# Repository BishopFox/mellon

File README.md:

## OSDP Vulnerabilities this Exploits
OSDP attack tool (and the Elvish word for friend)

### Attack #1: Encryption is Optional

OSDP supports, but doesn't strictly *require*, encryption. So your connection might not even be encrypted at all. Attack #1 is just to passively listen and see if you can read the card numbers on the wire.

### Attack #2: Downgrade Attack

Just because the controller and reader *support* encryption doesn't mean they're configured to *require* it be used. An attacker can modify the reader's capability reply message (osdp_PDCAP) to advertise that it doesn't support encryption. When this happens, some controllers will barrel ahead without encryption.

### Attack #3: Install-mode Attack

OSDP has a quasi-official “install mode” that applies to both readers and controllers. As the name suggests, it’s supposed to be used when first setting up a reader. What it does is essentially allow readers to ask the controller for what the base encryption key (the SCBK) is. If the controller is configured to be persistently in install-mode, then an attacker can show up on the wire and request the SCBK. 

### Attack #4: Weak Keys

OSDP sample code often comes with hardcoded encryption keys. Clearly these are meant to be samples, where the user is supposed to generate keys in a secure way on their own. But this is not explained or made simple for the user, however. And anyone who’s been in security long enough knows that whatever’s the default is likely to be there in production. 

So as an attack vector, when the link between reader and controller is encrypted, it’s worth a shot to enumerate some common weak keys. Now these are 128-bit AES keys, so we’re not going to be able to enumerate them all. Or even a meaningful portion of them. But what we can do is hit some common patterns that you see when someone hardcodes a key: 

- All single-byte values. [0x04, 0x04, 0x04, 0x04 …]
- All monotonically increasing byte values. [0x01, 0x02, 0x03, 0x04, …]
- All monotonically decreasing byte values. [0x0A, 0x09, 0x08, 0x07, …]

### Attack #5: Keyset Capture

OSDP has no in-band mechansim for key exchange. What this means is that an attacker can:

- Insert a covert listening device onto the wire. 
- Break / factory reset / disable the reader.
- Wait for someone from IT to come and replace the reader.
- Capture the keyset message (osdp_KEYSET) when the reader is first setup.
- Decrypt all future messages.

## Getting A Testbed Setup (Linux/MacOS)

You'll find proof-of-concept code for each of these attacks in `attack_osdp.py`. Checkout the `--help` command for more details on usage. This is a Python script, meant to be run from a laptop with USB<-->RS485 adapters [like one of these](https://www.amazon.com/Serial-Converter-Adapter-Supports-Windows/dp/B0195ZD3P4/). So you'll probably want to pick some of those up. Doesn't have to be that model, though.

If you have a controller you want to test, then great. Use that. If you don't, then we have an intentionally-vulnerable OSDP controller that you can use here: `vulnserver.py`. 

Some of the attacks in `attack_osdp.py` will expect to be as a full MitM between a functioning reader and controller. To test these, you might need *three* USB<-->RS485 adapters, hooked together with a breadboard.

### Additional Medium / Low Risk Issues

These issues are not, in isolation, exploitable but nonetheless represent a weakening of the protocol, implementation, or overall system.

- MACs are truncated to 32 bits "to reduce overhead". This is _very_ nearly (but not quite in our calculation) within practical exploitable range.
- IVs (which are derived from MACs) are similarly reduced to 32 bits of entropy. This will cause IV reuse, which is a big red flag for a protocol.
- Session keys are only generated using 48 bits of entropy from the controller RNG nonce. This appears to not be possible for an observing attacker to enumerate offline, however. (Unless we're missing something, in which case this would become a _critical_ issue.)
- Sequence numbers consist of only 2 bits, not providing sufficient liveness.
- CBC-mode encryption is used. GCM would be a more modern block cipher mode appropriate for network protocols.
- SCS modes 15 & 16 are essentially "null ciphers", and should not exist. They don't encrypt data.
- The OSDP command byte is always unencrypted, even in the middle of a Secure Channel session. This is a huge benefit to attackers, making attack tools much easier to write. It means that an attacker can always see what "type" of packet is being sent, even if it's otherwise encrypted. Attackers can tell when people badge in, when the LED lights up, etc... This is not information that should be in plaintext.
- SCBK-D (a hardcoded "default" encryption key) provides no security and should be removed. It serves only to obfuscate and provide a false sense of security.

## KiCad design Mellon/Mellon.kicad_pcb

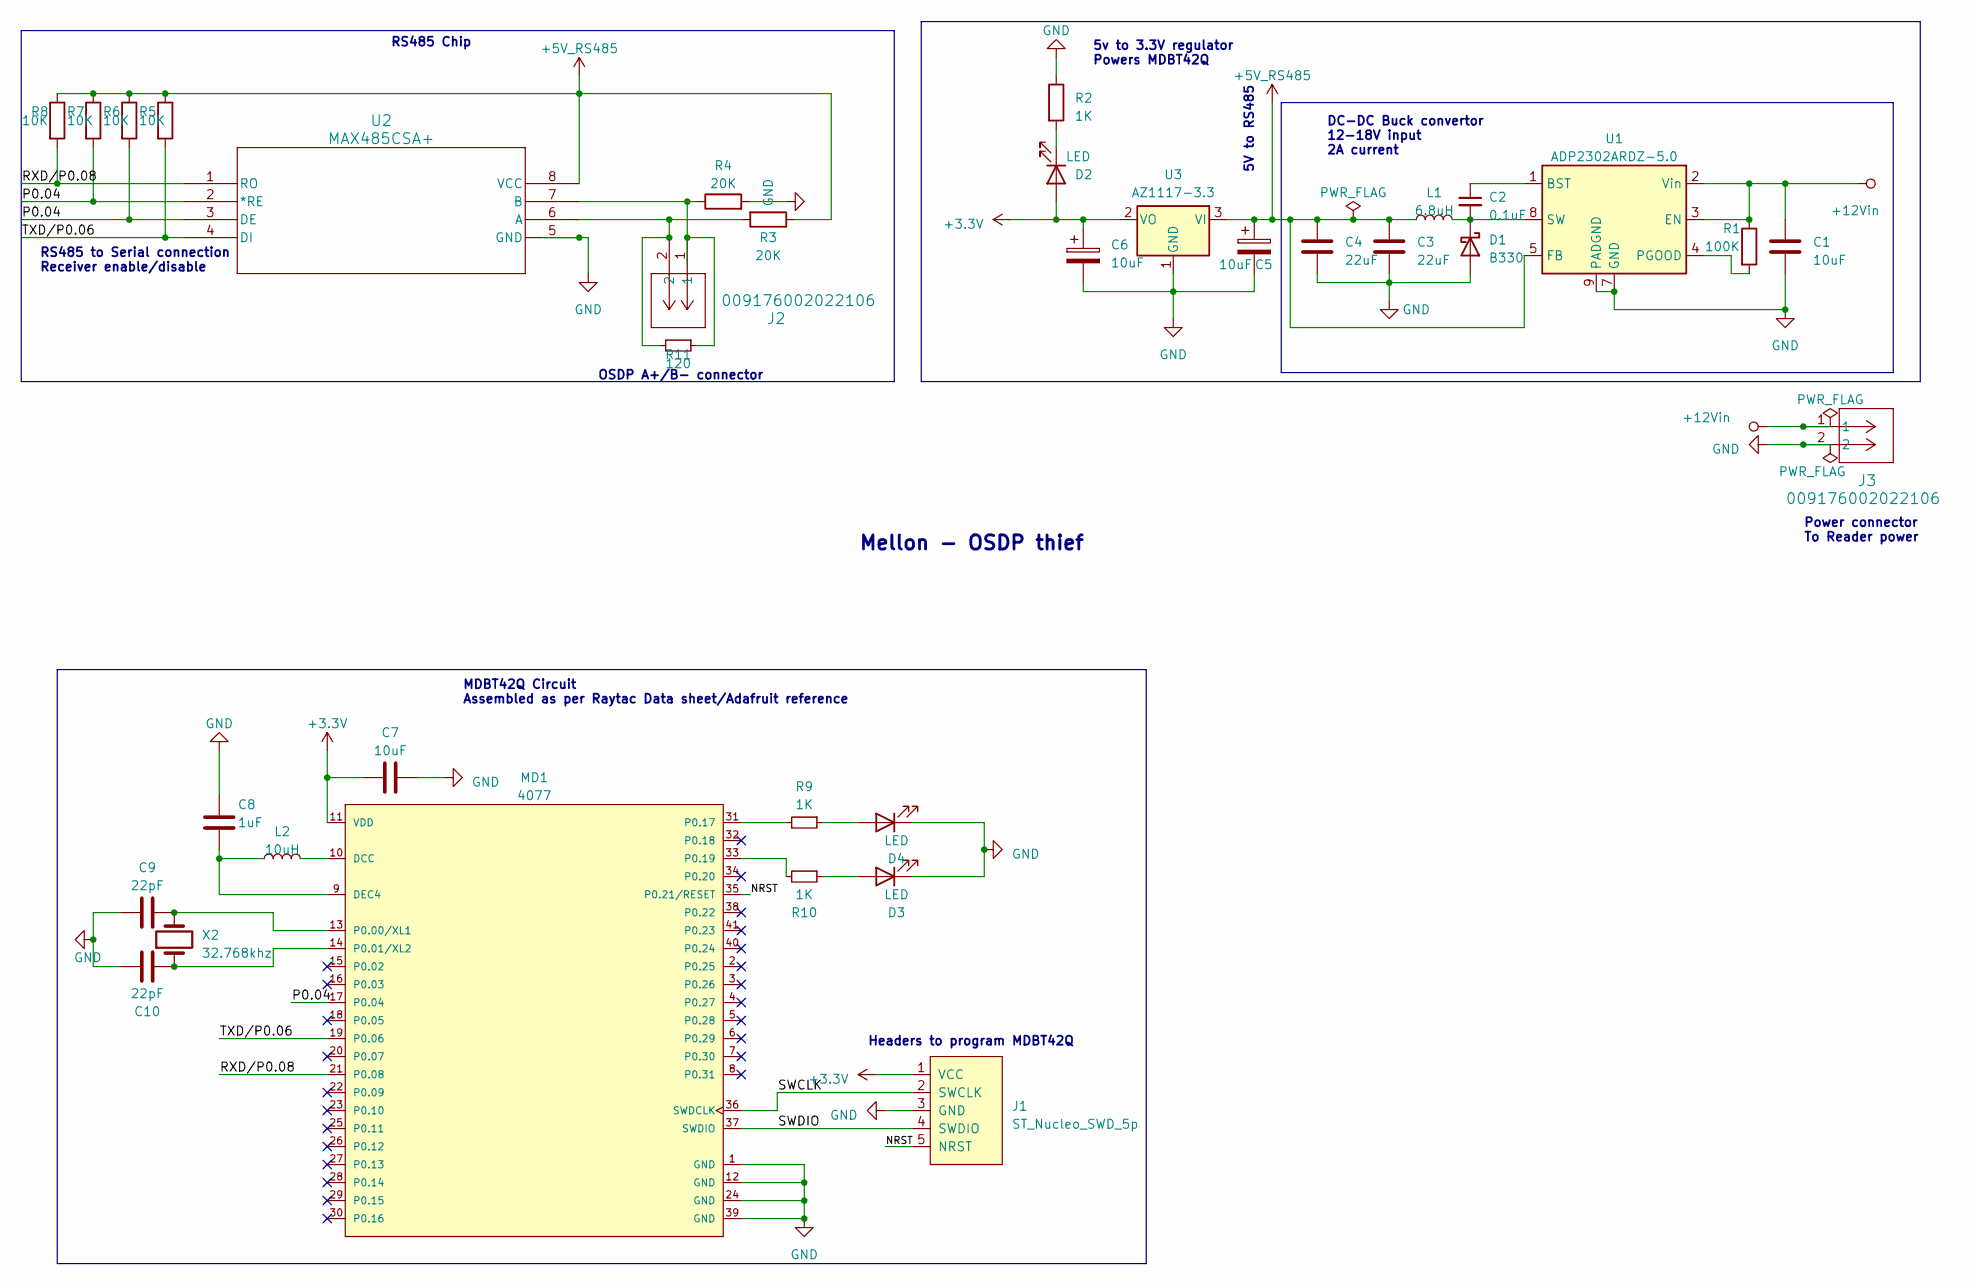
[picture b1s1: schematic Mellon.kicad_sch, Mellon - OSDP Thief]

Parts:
C1, C7: 10uF; C_0603_1608Metric
C2: 0.1uF; C_0603_1608Metric
C3, C4: 22uF; C_0603_1608Metric
C5, C6: 10uF; CP_EIA-3216-18_Kemet-A
C8: 1uF; C_0603_1608Metric
C9, C10: 22pF; C_0603_1608Metric
D1: B330; D_SMA
D2, D3, D4: LED; D_0603_1608Metric
J1: ST_Nucleo_SWD_5p; PinHeader_1x05_P2.54mm_Vertical
J2, J3: 009176002022106; CONN_9176_2WAY_KYO
L1: 6.8uH; L_TDK_VLS6045EX_VLS6045AF
L2: 10uH; L_1008_2520Metric
MD1: 4077; Adafruit_Industries-4077-*; mouser part number 485-4077; digikey description RX TXRX MOD BLUETOOTH CHIP SMD
R1: 100K; R_0603_1608Metric
R2, R9, R10: 1K; R_0603_1608Metric
R3, R4: 20K; R_0603_1608Metric
R5, R6, R7, R8: 10K; R_0603_1608Metric
R11: 120; R_0603_1608Metric
U1: ADP2302ARDZ-5.0; SOIC-8-1EP_3.9x4.9mm_P1.27mm_EP2.29x3mm
U2: MAX485CSA+; 21-0041B_8_MXM
U3: AZ1117-3.3; SOT-223
X2: 32.768khz; Crystal_SMD_MicroCrystal_CC7V-T1A-2Pin_3.2x1.5mm

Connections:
+3.3V: C6.1, C7.2, D2.2 (A), J1.1 (VCC), MD1.11 (VDD), U3.2 (VO)
+5V_RS485: C3.1, C4.2, C5.1, L1.1, R3.1, R5.1, R6.1, R7.1, R8.1, U1.5 (FB), U2.8 (VCC), U3.3 (VI)
+12Vin: C1.1, J3.1, R1.1, U1.2 (Vin), U1.3 (EN)
/NRST: J1.5 (NRST), MD1.35 (P0.21/RESET)
/P0.04: MD1.17 (P0.04), R6.2, R7.2, U2.2 (*RE), U2.3 (DE)
/RXD/P0.08: MD1.21 (P0.08), R8.2, U2.1 (RO)
/SWCLK: J1.2 (SWCLK), MD1.36 (SWDCLK)
/SWDIO: J1.4 (SWDIO), MD1.37 (SWDIO)
/TXD/P0.06: MD1.19 (P0.06), R5.2, U2.4 (DI)
GND: C1.2, C3.2, C4.1, C5.2, C6.2, C7.1, C8.1, C9.1, C10.1, D1.2 (A), D3.1 (K), D4.1 (K), J1.3 (GND), J3.2, MD1.1 (GND), MD1.12 (GND), MD1.24 (GND), MD1.39 (GND), R2.1, R4.2, U1.7 (GND), U1.9 (PADGND), U2.5 (GND), U3.1 (GND)
unnamed: C2.2, D1.1 (K), L1.2, U1.8 (SW)
unnamed: D2.1 (K), R2.2
unnamed: D3.2 (A), R10.1
unnamed: D4.2 (A), R9.1
unnamed: L2.2, MD1.10 (DCC)
unnamed: C8.2, L2.1, MD1.9 (DEC4)
unnamed: C9.2, MD1.13 (P0.00/XL1), X2.2
unnamed: C10.2, MD1.14 (P0.01/XL2), X2.1
unnamed: MD1.31 (P0.17), R9.2
unnamed: MD1.33 (P0.19), R10.2
unnamed: C2.1, U1.1 (BST)
unnamed: R1.2, U1.4 (PGOOD)
unnamed: J2.2, R3.2, R11.2, U2.6 (A)
unnamed: J2.1, R4.1, R11.1, U2.7 (B)

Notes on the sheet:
MDBT42Q Circuit Assembled as per Raytac Data sheet/Adafruit reference
RS485 to Serial connection Receiver enable/disable
Power connector To Reader power
OSDP A+/B- connector
Headers to program MDBT42Q
DC-DC Buck convertor 12-18V input 2A current
5V to RS485
5v to 3.3V regulator Powers MDBT42Q
RS485 Chip
Mellon - OSDP thief

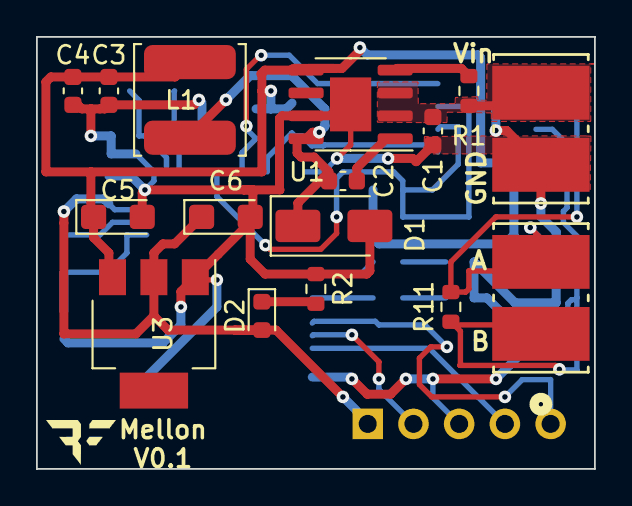
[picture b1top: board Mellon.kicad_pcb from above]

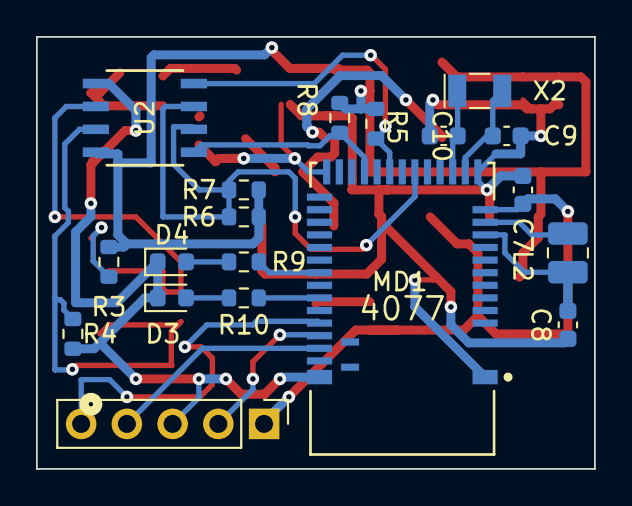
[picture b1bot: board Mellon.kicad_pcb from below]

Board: 2 copper layers, 31.0 x 24.0 mm, 35 parts (19 on the bottom side), 24 nets.

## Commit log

2023-08-12 Kicad Upload
2023-08-15 Update readme with medium / low risk issues
